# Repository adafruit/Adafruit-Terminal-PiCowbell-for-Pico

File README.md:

## Adafruit Terminal PiCowbell for Pico - Reset Button & STEMMA QT PCB

<a href="http://www.adafruit.com/products/5904"><br/>
Click here to purchase one from the Adafruit shop</a>

PCB files for the Adafruit Terminal PiCowbell for Pico - Reset Button & STEMMA QT. 

Format is EagleCAD schematic and board layout
* https://www.adafruit.com/product/5904

### Description

Ding dong! Hear that? It's the PiCowbell ringing, letting you know that the new Adafruit Terminal PiCowbell is finally in stock and ready to assist your Raspberry Pi Pico and Pico W project with handy hardware and practical prototyping with screw terminal blocks for each and every pin.

This board is ideal for when you want quick access to connect solid or stranded core wires to any of the GPIO pads on the Pico. We use four 10-pin 2.54" pitch screw terminal blocks that can fit 18~26 AWG solid or stranded core wires. Note that we really connect every pin 1-to-1 so there will be plenty of ground connects!

Please Note! To keep things flexible, this PiCowbell does not come with socket or pin headers, even though we have some example photos with not-included socket headers installed. There are many possible configurations, and we stock various headers depending on how you want to solder and attach them. This is especially true if you want the Pico on top so that the BOOTSEL button and LED are accessible.

Use the Pico Stacking Headers if you want to plug into a breadboard or other accessory with sockets.
Use the Pico Socket Headers if you want to plug directly in and have a nice, solid connection without any poking-out bits.
Use the Short Socket Headers for a very slim but pluggable design, note that you'll want to trim down the Pico's headers or use the short plug headers on the Pico to have a skinny sandwich.
Solder the PCB directly to the Pico headers - of course, this is very compact and inexpensive, but you won't be able to remove the PiCowbell.
The Terminal PiCowbell provides you with:

* Screw Terminal blocks for each matching pad on the Pico or Pico W: 40 total pins, 40 total blocks
* Right angle reset button that sticks out the end
* Right angle JST SH connector for I2C / Stemma QT / Qwiic connection. Or can use it for plain GPIO wiring if you don't have any I2C devices to attach. Provides 3V, GND, IO4 (SDA), and IO5 (SCL)
* There is an extra set of 4 breakout holes next to the JST SH in case you want more I2C connections or want to re-assign the I2C port.
* 15 rows of 8-hole connected strips in the center area. You can cut the traces between the holes, but they're intended to be treated like a mini-mini breadboard
* Every pad on the Pico has a duplicate hole pad next to it for solder-jumpering
* The ground pads have white silkscreen rectangles to easily identify, plus one long ground strip near the reset button
* One long strip of connected holes for 3.3V power
* Gold-plated pads for easy soldering

We do not have I2C pullups on the board, but your Qwiic/QT breakout board or accessory likely already has them onboard. If using the Philhower Arduino core, the Wire peripheral is already set up to use IO4 and IO5. If using CircuitPython or MicroPython, you'll need to let the code know to look at 4+5 for SDA+SCL pins.

### License

Adafruit invests time and resources providing this open source design, please support Adafruit and open-source hardware by purchasing products from [Adafruit](https://www.adafruit.com)!

Designed by Limor Fried/Ladyada for Adafruit Industries.

Creative Commons Attribution/Share-Alike, all text above must be included in any redistribution. 
See license.txt for additional details.

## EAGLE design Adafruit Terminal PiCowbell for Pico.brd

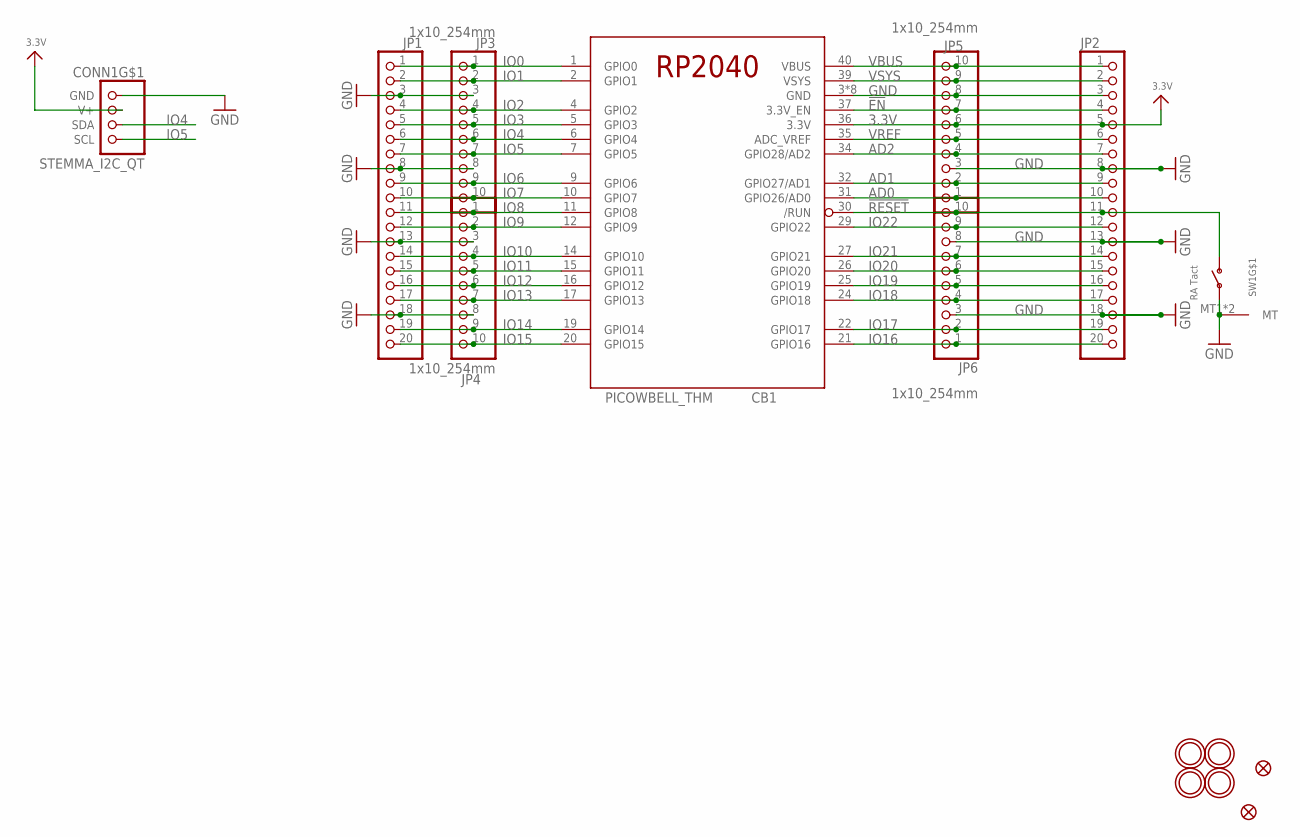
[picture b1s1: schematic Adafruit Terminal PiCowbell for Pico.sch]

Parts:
CB1: PICOWBELL_THM
CONN1: STEMMA_I2C_QT; JST_SH4
FID1, FID2: FIDUCIAL_1MM
JP1, JP2: HEADER-1X20_70MIL; 1X20_ROUND_70MIL
JP3, JP4, JP5, JP6: 1x10_254mm; 1X10_2.54MMTERMINAL
SW1: RA Tact; SPST_TACTILE_RA
U$5, U$7, U$8, U$9: MOUNTINGHOLE3.0THIN; MOUNTINGHOLE_3.0_PLATEDTHIN

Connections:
3.3V: CB1.36 (3.3V), CONN1.2 (V+), JP2.5, JP5.6
!EN: CB1.37 (3.3V_EN), JP2.4, JP5.7
!RESET: CB1.30 (/RUN), JP2.11, JP6.10, SW1.2 (S)
AD0: CB1.31 (GPIO26/AD0), JP2.10, JP5.1
AD1: CB1.32 (GPIO27/AD1), JP2.9, JP5.2
AD2: CB1.34 (GPIO28/AD2), JP2.7, JP5.4
GND: CB1.3 (GND), CB1.8 (GND), CB1.13 (GND), CB1.18 (GND), CB1.23 (GND), CB1.28 (GND), CB1.33 (GND), CB1.38 (GND), CONN1.1 (GND), JP1.3, JP1.8, JP1.13, JP1.18, JP2.3, JP2.8, JP2.13, JP2.18, JP3.3, JP3.8, JP4.3, JP4.8, JP5.3, JP5.8, JP6.3, JP6.8, SW1.1, SW1.MT1 (MT), SW1.MT2 (MT)
IO0: CB1.1 (GPIO0), JP1.1, JP3.1
IO1: CB1.2 (GPIO1), JP1.2, JP3.2
IO2: CB1.4 (GPIO2), JP1.4, JP3.4
IO3: CB1.5 (GPIO3), JP1.5, JP3.5
IO4: CB1.6 (GPIO4), CONN1.3 (SDA), JP1.6, JP3.6
IO5: CB1.7 (GPIO5), CONN1.4 (SCL), JP1.7, JP3.7
IO6: CB1.9 (GPIO6), JP1.9, JP3.9
IO7: CB1.10 (GPIO7), JP1.10, JP3.10
IO8: CB1.11 (GPIO8), JP1.11, JP4.1
IO9: CB1.12 (GPIO9), JP1.12, JP4.2
IO10: CB1.14 (GPIO10), JP1.14, JP4.4
IO11: CB1.15 (GPIO11), JP1.15, JP4.5
IO12: CB1.16 (GPIO12), JP1.16, JP4.6
IO13: CB1.17 (GPIO13), JP1.17, JP4.7
IO14: CB1.19 (GPIO14), JP1.19, JP4.9
IO15: CB1.20 (GPIO15), JP1.20, JP4.10
IO16: CB1.21 (GPIO16), JP2.20, JP6.1
IO17: CB1.22 (GPIO17), JP2.19, JP6.2
IO18: CB1.24 (GPIO18), JP2.17, JP6.4
IO19: CB1.25 (GPIO19), JP2.16, JP6.5
IO20: CB1.26 (GPIO20), JP2.15, JP6.6
IO21: CB1.27 (GPIO21), JP2.14, JP6.7
IO22: CB1.29 (GPIO22), JP2.12, JP6.9
VBUS: CB1.40 (VBUS), JP2.1, JP5.10
VREF: CB1.35 (ADC_VREF), JP2.6, JP5.5
VSYS: CB1.39 (VSYS), JP2.2, JP5.9

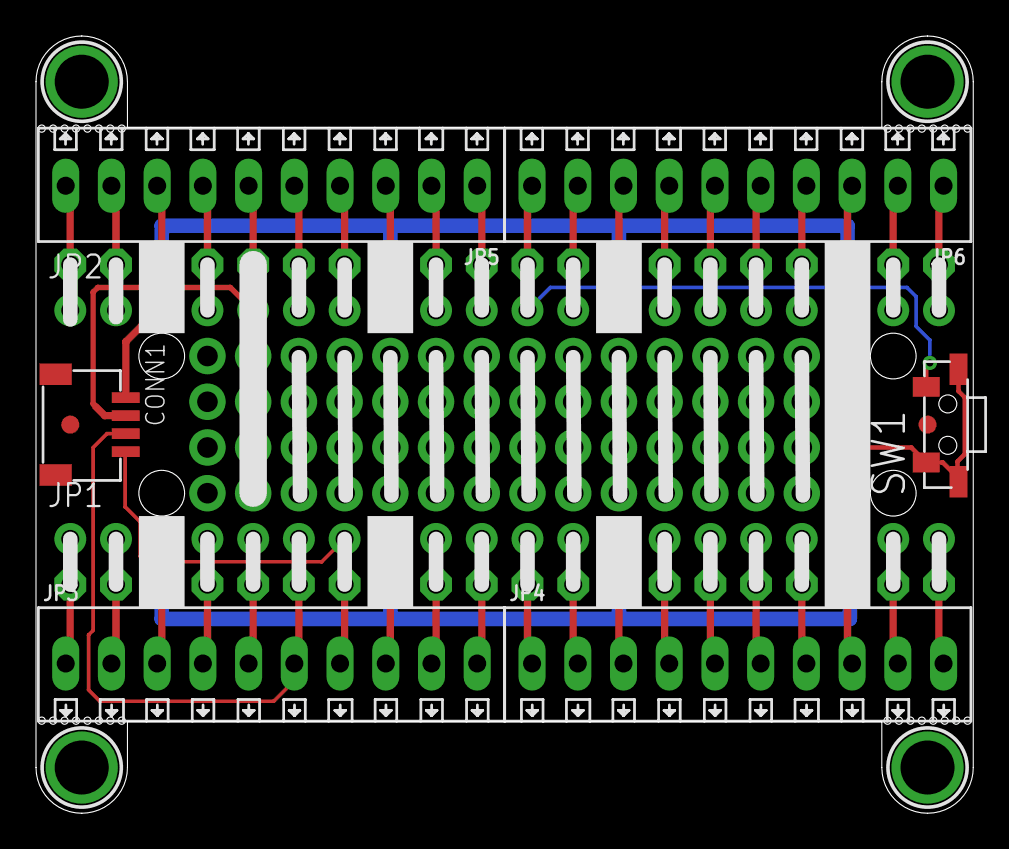
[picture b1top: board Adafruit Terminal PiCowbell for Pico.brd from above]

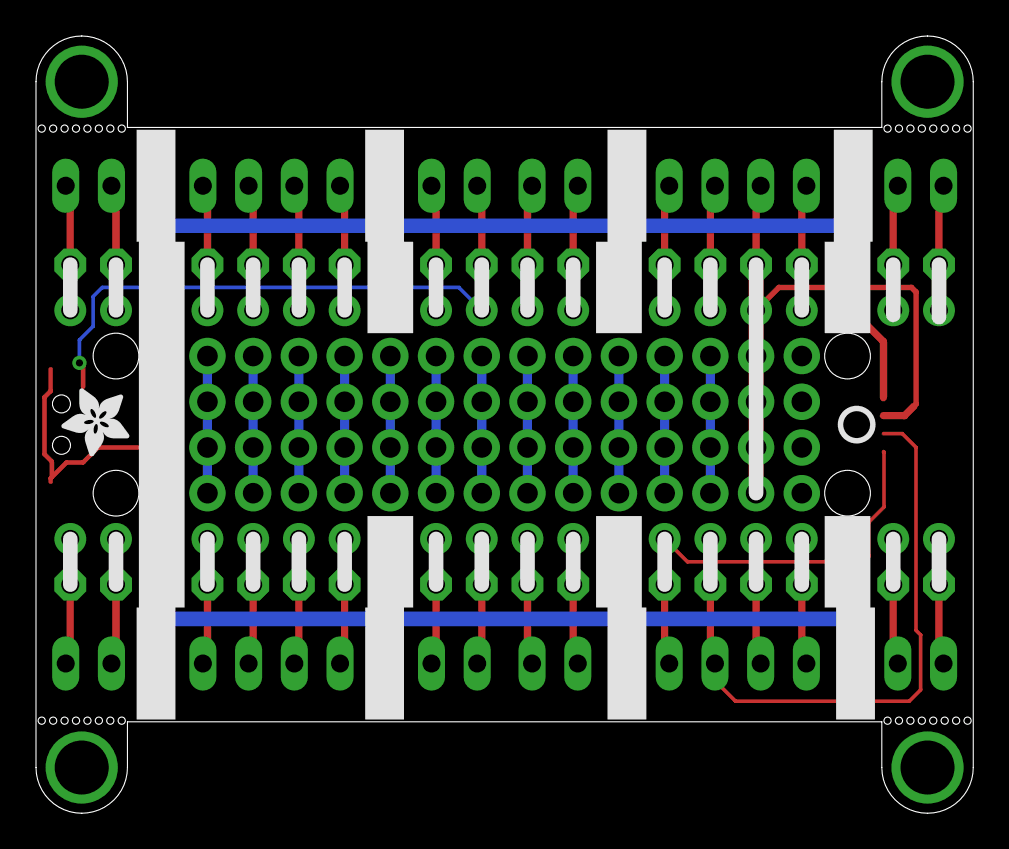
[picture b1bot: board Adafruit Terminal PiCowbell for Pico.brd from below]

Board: 2 copper layers, 52.1 x 43.2 mm, 105 parts (61 on the bottom side), 33 nets.

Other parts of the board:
E$1: ADAFRUIT_3.5MM
PLABEL0: PLABEL0
PLABEL1: PLABEL1
PLABEL2: PLABEL2
PLABEL3: PLABEL3
PLABEL4: PLABEL4
PLABEL5: PLABEL5
PLABEL6: PLABEL6
PLABEL7: PLABEL7
PLABEL8: PLABEL8
PLABEL9: PLABEL9
PLABEL10: PLABEL10
PLABEL11: PLABEL11
PLABEL12: PLABEL12
PLABEL13: PLABEL13
PLABEL14: PLABEL14
PLABEL15: PLABEL15
PLABEL17: PLABEL17
PLABEL19: PLABEL19
PLABEL20: PLABEL20
PLABEL21: PLABEL21
PLABEL22: PLABEL22
PLABEL23: PLABEL23
PLABEL24: PLABEL24
PLABEL25: PLABEL25
PLABEL26: PLABEL26
PLABEL27: PLABEL27
PLABEL28: PLABEL28
PLABEL29: PLABEL29
PLABEL30: PLABEL30
PLABEL35, PLABEL36: PLABEL36
PLABEL37, PLABEL68: PLABEL37
PLABEL38, PLABEL69: PLABEL38
PLABEL39, PLABEL70: PLABEL39
PLABEL40, PLABEL71: PLABEL40
PLABEL41, PLABEL72: PLABEL41
PLABEL42, PLABEL73: PLABEL42
PLABEL43, PLABEL74: PLABEL43
PLABEL44, PLABEL75: PLABEL44
PLABEL45, PLABEL76: PLABEL45
PLABEL46, PLABEL94: PLABEL46
PLABEL47, PLABEL93: PLABEL47
PLABEL48, PLABEL92: PLABEL48
PLABEL49, PLABEL88: PLABEL49
PLABEL50, PLABEL81: PLABEL50
PLABEL52, PLABEL82: PLABEL52
PLABEL54, PLABEL87: PLABEL54
PLABEL55, PLABEL86: PLABEL55
PLABEL56, PLABEL84: PLABEL56
PLABEL57, PLABEL77: PLABEL57
PLABEL58, PLABEL78: PLABEL58
PLABEL59, PLABEL85: PLABEL59
PLABEL60, PLABEL79: PLABEL60
PLABEL61, PLABEL89: PLABEL61
PLABEL62, PLABEL90: PLABEL62
PLABEL63, PLABEL91: PLABEL63
PLABEL64: PLABEL64
PLABEL65: PLABEL65
PLABEL66: PLABEL66
PLABEL67: PLABEL67
PLABEL80: PLABEL51
PLABEL83: PLABEL53
PLABEL688: PLABEL688
U$6: PCBFEAT-REV-040

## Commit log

2024-03-14 cookiecutter

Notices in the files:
parts and their libraries:
microbuilder: This work is placed in the public domain, and may be freely used for commercial and non-commercial work with the following conditions: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
